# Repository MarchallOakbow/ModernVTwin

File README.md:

# ModernVTwin
The project to make Mesa V-Twin Pedal<br>
First Upload 19th Aug 2016<br>

<li>How to open schematic file</li>
Download CAD soft eagle from here <a href = "https://cadsoft.io/">eagle.io</a><br>
Copy the repository or Download .sch file. And Open it with EagleCAD software.<br>

<li>Current status</li>
The circuit is designed based on the Mesa V-twin.<br>
The power supply & mode switch circuit is changed according to current available parts in Japan.<br>

<li>Changes coming soon...</li>
DRC check<br>
Extract BOM<br>
Parts layout check<br>
Pattern Drawing<br>
PCB design<br>

I would like to foward this project with many hobbyist over the world.<br>
Contact me on twitter <a href = "https://twitter.com/MarChallenge">@MarChallenge</a>.<br>

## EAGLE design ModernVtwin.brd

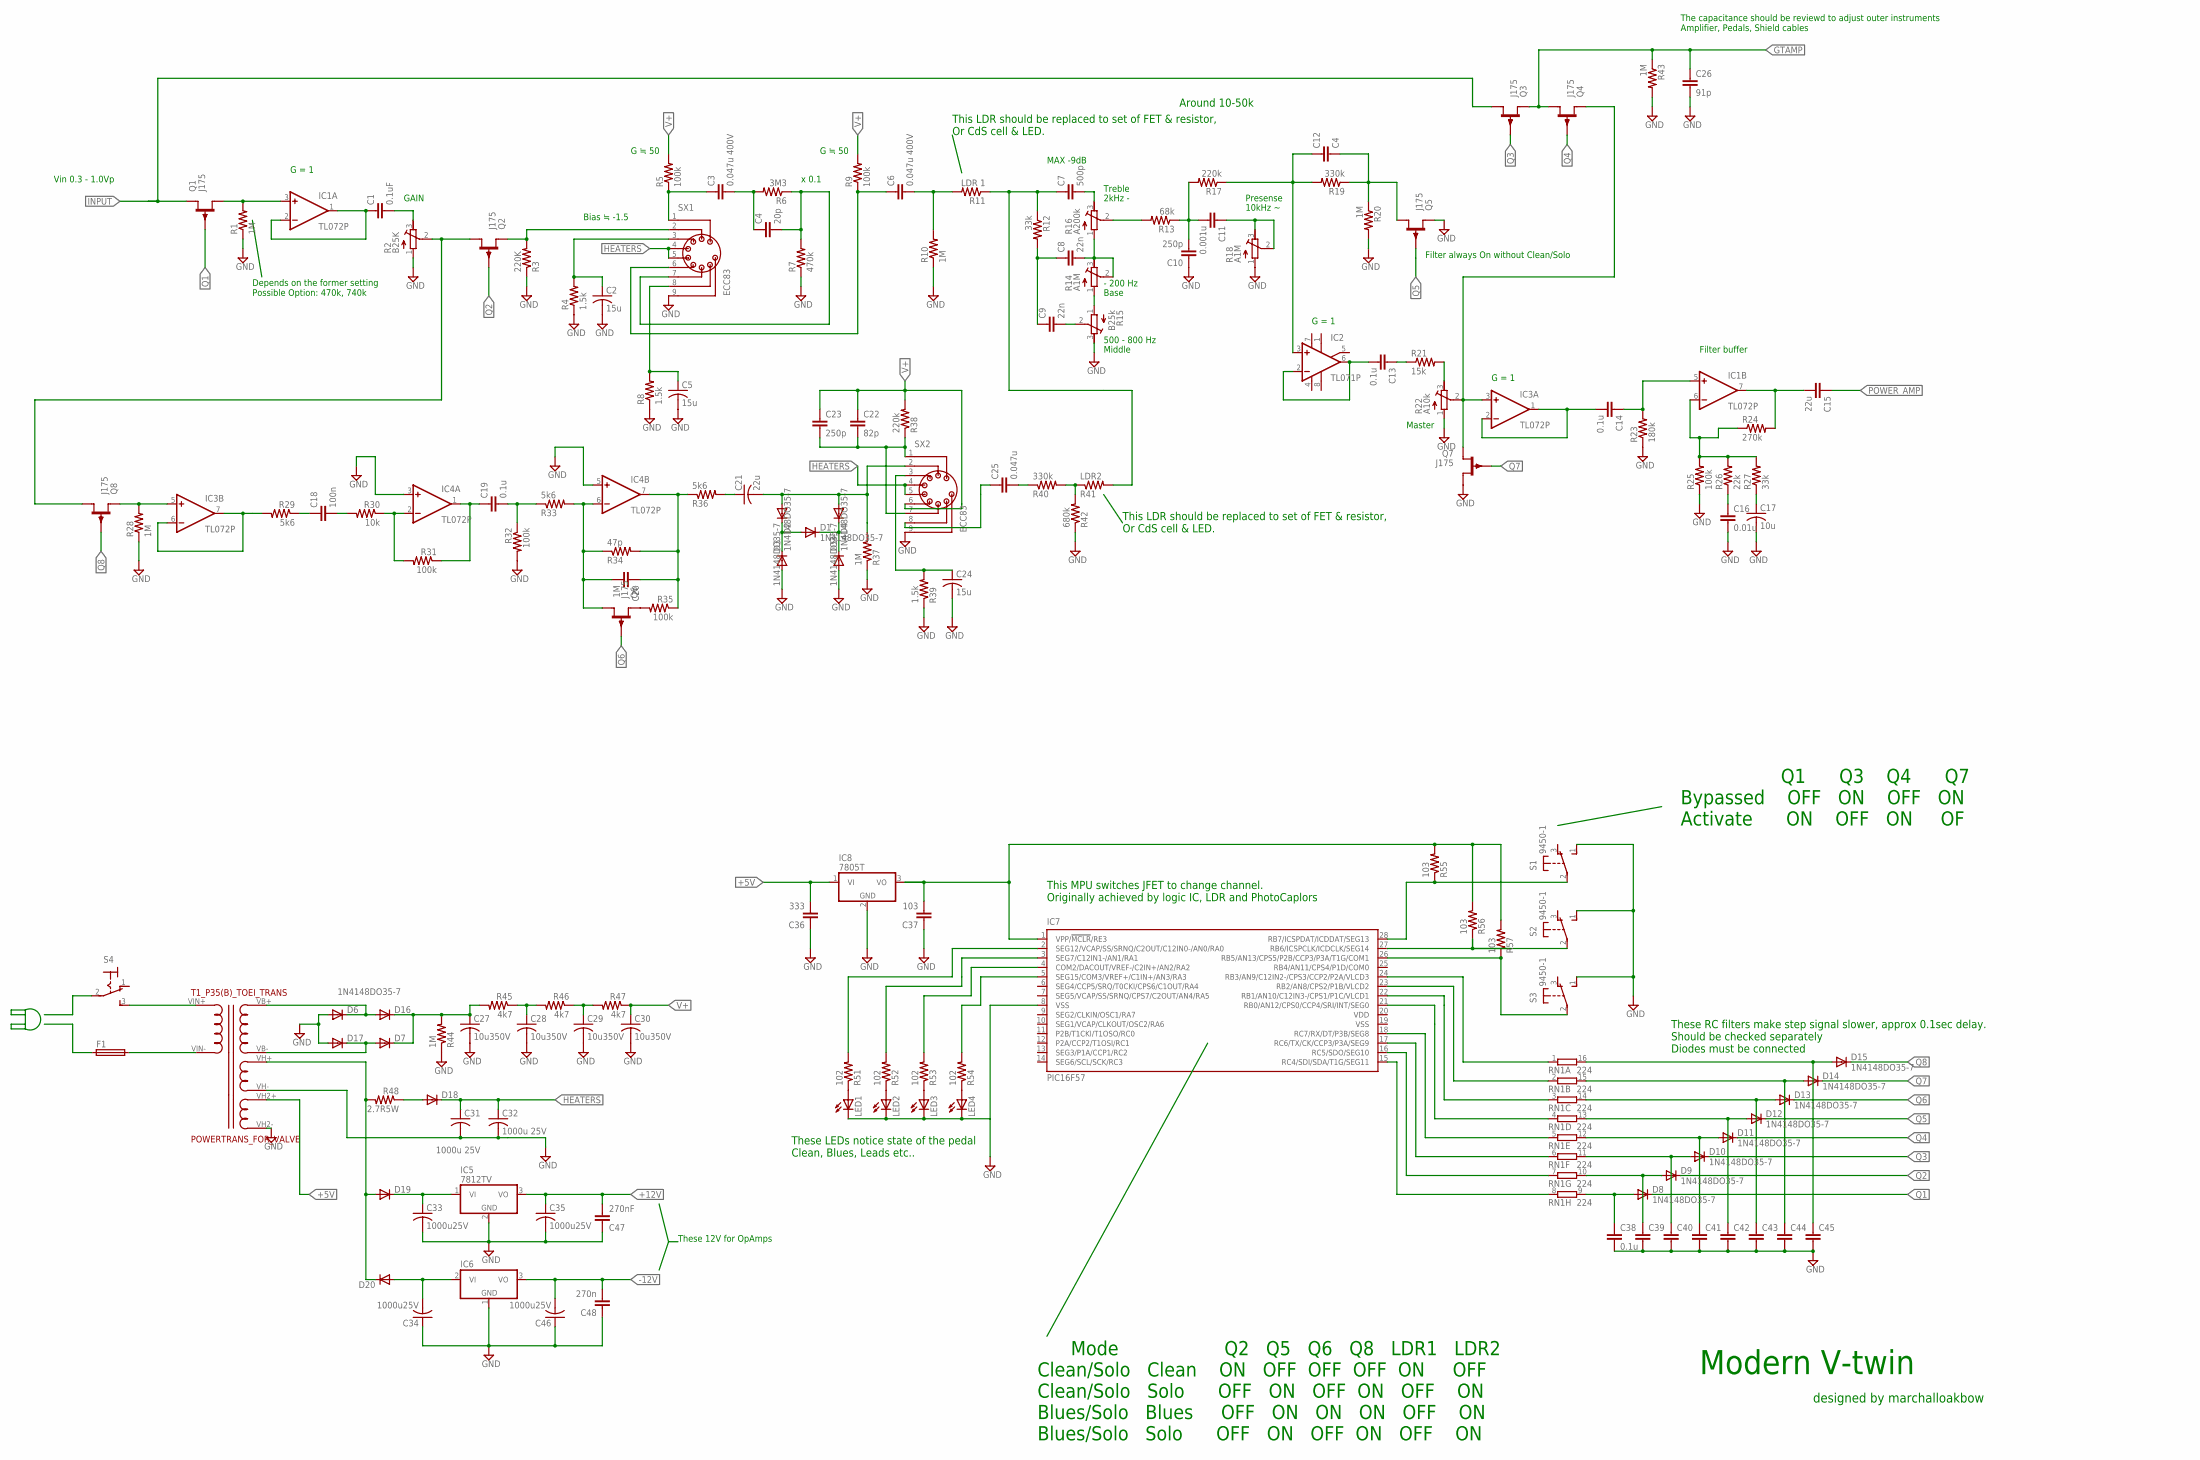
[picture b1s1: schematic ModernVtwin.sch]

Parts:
C1: 0.1uF; C5B3
C2, C5, C24: 15u; C025-025X050
C3, C6: 0.047u 400V; C5B3
C4: 20p; C5B3
C7: 500p; C5B3
C8, C9: 22n; C5B3
C10, C23: 250p; C5B3
C11: 0.001u; C5B3
C12: C4; C5B3
C13, C14, C19: 0.1u; C5B3
C15: 22u; C5B3
C16: 0.01u; C5B3
C17: 10u; C025-025X050
C18: 100n; C5B3
C20: 1M; C5B3
C21: 22u; C025-025X050
C22: 82p; C5B3
C25: 0.047u; C5B3
C26: 91p; C5B3
C27, C28, C29, C30: 10u350V; C025-025X050
C31, C32: 1000u 25V; C025-025X050
C33, C34, C35, C46: 1000u25V; C025-025X050
C36: 333; C5B3
C37: 103; C5B3
C38: 0.1u; C025-024X044
C39, C40, C41, C42, C43, C44, C45: C-EU025-024X044; C025-024X044
C47: 270nF; C5B3
C48: 270n; C5B3
D1, D2, D3, D4, D5, D6, D7, D8, D9, D10, D11, D12, D13, D14, D15, D16, D17, D18, D19, D20: 1N4148DO35-7; DO35-7
F1: SH22,5
IC1, IC3, IC4: TL072P; DIL08
IC2: TL071P; DIL08
IC5: 7812TV; TO220V
IC6: 7912T; TO220H
IC7: PIC16F57; DIL28-3
IC8: 7805T; TO220H
LED1, LED2, LED3, LED4: LED5MM
Q1, Q2, Q3, Q4, Q5, Q6, Q7, Q8: J175; TO92F
R1, R10, R20, R28, R37, R43, R44: 1M; 0204V
R2: B25K; RTRIM64W
R3: 220K; 0204V
R4, R8, R39: 1.5k; 0204V
R5, R9, R25, R31, R32, R35: 100k; 0204V
R6: 3M3; 0204V
R7: 470k; 0204V
R11: LDR 1; 0204V
R12, R27: 33k; 0204V
R13: 68k; 0204V
R14, R18: A1M; RTRIM64W
R15: B25k; RTRIM64W
R16: A200k; RTRIM64W
R17, R38: 220k; 0204V
R19, R40: 330k; 0204V
R21: 15k; 0204V
R22: A10k; RTRIM64W
R23: 180k; 0204V
R24: 270k; 0204V
R26: 22k; 0204V
R29, R33, R36: 5k6; 0204V
R30: 10k; 0204V
R34: 47p; 0204V
R41: LDR2; 0204V
R42: 680k; 0204V
R45, R46, R47: 4k7; 0204V
R48: 2.7R5W; 0204V
R51, R52, R53, R54: 102; 0204V
R55, R56, R57: 103; 0204V
RN1: 224; DIL16
S1, S2, S3: 9450-1
S4: M9040P
SX1, SX2: ECC83; VT9-PT
T1_P35(B)_TOEI_TRANS: POWERTRANS_FOR_VALVE; POWERTRANS

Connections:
+5V: C36.2, IC8.1 (VI), T1_P35(B)_TOEI_TRANS.VH2+
+12V: C35.1, C47.2, IC5.3 (VO)
-12V: C46.2, C48.2, IC6.3 (VO)
GND: C2.2, C5.2, C10.1, C16.2, C17.2, C24.2, C26.2, C27.2, C28.2, C29.2, C30.2, C31.2, C32.2, C33.2, C34.1, C35.2, C36.1, C37.1, C38.2, C39.2, C40.2, C41.2, C42.2, C43.2, C44.2, C45.2, C46.1, C47.1, C48.1, D3.A, D5.A, D6.A, D17.A, IC4.3 (+IN), IC4.5 (+IN), IC5.2 (GND), IC6.1 (GND), IC7.8 (VSS), IC8.2 (GND), LED1.K (C), LED2.K (C), LED3.K (C), LED4.K (C), Q5.S, Q7.D, R1.1, R2.1 (E), R3.1, R4.1, R7.1, R8.1, R10.1, R15.3 (A), R18.1 (E), R20.2, R22.1 (E), R23.1, R25.1, R28.1, R32.2, R37.1, R39.1, R42.1, R43.2, R44.1, S1.1 (S), S2.1 (S), S3.1 (S), SX1.9, SX2.9, T1_P35(B)_TOEI_TRANS.VH2-, T1_P35(B)_TOEI_TRANS.VH-
GTAMP: C26.1, Q3.S, Q4.D, R43.1
HEATERS: C31.1, C32.1, D18.C, SX1.4, SX1.5, SX2.4, SX2.5
INPUT: Q1.S, Q3.D
unnamed: IC1.3 (+IN), Q1.D, R1.2
unnamed: C1.1, IC1.1 (OUT), IC1.2 (-IN)
unnamed: C1.2, R2.3 (A)
unnamed: Q2.D, Q8.D, R2.2 (S)
unnamed: Q2.S, R3.2, SX1.2
unnamed: C2.1, R4.2, SX1.3
unnamed: C3.1, R5.1, SX1.1
unnamed: C3.2, C4.1, R6.2
unnamed: C4.2, R6.1, R7.2, SX1.7
unnamed: R13.2, R16.2 (S)
unnamed: C5.1, R8.2, SX1.8
unnamed: C6.1, R9.1, SX1.6
unnamed: C6.2, R10.2, R11.2
unnamed: C10.2, C11.2, R13.1, R17.2
unnamed: C7.1, R11.1, R12.1, R41.2
unnamed: C8.1, C9.1, R12.2
unnamed: C9.2, R15.2 (S)
unnamed: C8.2, R14.2 (S), R14.3 (A), R16.1 (E)
unnamed: C7.2, R16.3 (A)
unnamed: R14.1 (E), R15.1 (E)
unnamed: C11.1, R18.2 (S), R18.3 (A)
unnamed: C12.1, IC2.3 (+IN), R17.1, R19.2
unnamed: C12.2, Q5.D, R19.1, R20.1
unnamed: IC3.5 (+IN), Q8.S, R28.2
unnamed: C13.2, IC2.2 (-IN), IC2.6 (OUT)
unnamed: C13.1, R21.1
unnamed: R21.2, R22.3 (A)
unnamed: IC3.3 (+IN), Q4.S, Q7.S, R22.2 (S)
unnamed: C14.2, IC3.1 (OUT), IC3.2 (-IN)
unnamed: C14.1, IC1.5 (+IN), R23.2
unnamed: IC1.6 (-IN), R24.1, R25.2, R26.2, R27.2
unnamed: C15.2, IC1.7 (OUT), R24.2
unnamed: C16.1, R26.1
unnamed: C17.1, R27.1
unnamed: IC3.6 (-IN), IC3.7 (OUT), R29.2
unnamed: C18.1, R29.1
unnamed: C18.2, R30.2
unnamed: IC4.2 (-IN), R30.1, R31.2
unnamed: C20.2, IC4.6 (-IN), Q6.D, R33.2, R34.1
unnamed: C19.2, R32.1, R33.1
unnamed: C19.1, IC4.1 (OUT), R31.1
unnamed: Q6.S, R35.2
unnamed: C20.1, IC4.7 (OUT), R34.2, R35.1, R36.1
unnamed: C21.1, R36.2
unnamed: C21.2, D2.A, D4.A, R37.2, SX2.2
unnamed: D1.A, D2.C, D3.C
unnamed: D1.C, D4.C, D5.C
unnamed: C22.2, C23.2, R38.1, SX2.1, SX2.7
unnamed: C25.2, R40.1
unnamed: R40.2, R41.1, R42.2
unnamed: C24.1, R39.2, SX2.3
unnamed: C25.1, SX2.8
unnamed: C37.2, IC7.1 (VPP/!MCLR!/RE3), IC8.3 (VO), R55.2, R56.2, R57.2
unnamed: S4.3 (S), T1_P35(B)_TOEI_TRANS.VIN+ (100VIN+)
unnamed: F1.2, T1_P35(B)_TOEI_TRANS.VIN- (100VIN-)
unnamed: D6.C, D16.A, T1_P35(B)_TOEI_TRANS.VB+
unnamed: D19.A, D20.C, R48.2, T1_P35(B)_TOEI_TRANS.VH+
unnamed: C27.1, D7.C, D16.C, R44.2, R45.2
unnamed: C28.1, R45.1, R46.2
unnamed: IC7.15 (RC4/SDI/SDA/T1G/SEG11), RN1.8 (1)
unnamed: C29.1, R46.1, R47.2
unnamed: D18.A, R48.1
unnamed: IC7.16 (RC5/SDO/SEG10), RN1.7 (1)
unnamed: IC7.17 (RC6/TX/CK/CCP3/P3A/SEG9), RN1.6 (1)
unnamed: IC7.18 (RC7/RX/DT/P3B/SEG8), RN1.5 (1)
unnamed: IC7.21 (RB0/AN12/CPS0/CCP4/SRI/INT/SEG0), RN1.4 (1)
unnamed: IC7.22 (RB1/AN10/C12IN3-/CPS1/P1C/VLCD1), RN1.3 (1)
unnamed: IC7.23 (RB2/AN8/CPS2/P1B/VLCD2), RN1.2 (1)
unnamed: IC7.24 (RB3/AN9/C12IN2-/CPS3/CCP2/P2A/VLCD3), RN1.1
unnamed: IC7.28 (RB7/ICSPDAT/ICDDAT/SEG13), R55.1, S1.2
unnamed: IC7.26 (RB5/AN13/CPS5/P2B/CCP3/P3A/T1G/COM1), R57.1, S3.2
unnamed: LED1.A, R51.1
unnamed: LED2.A, R52.1
unnamed: LED3.A, R53.1
unnamed: LED4.A, R54.1
unnamed: IC7.2 (SEG12/VCAP/SS/SRNQ/C2OUT/C12IN0-/AN0/RA0), R51.2
unnamed: IC7.3 (SEG7/C12IN1-/AN1/RA1), R52.2
unnamed: IC7.4 (COM2/DACOUT/VREF-/C2IN+/AN2/RA2), R53.2
unnamed: IC7.5 (SEG15/COM3/VREF+/C1IN+/AN3/RA3), R54.2
unnamed: C38.1, D8.A, RN1.9 (2)
unnamed: C39.1, D9.A, RN1.10 (2)
unnamed: C40.1, D10.A, RN1.11 (2)
unnamed: C41.1, D11.A, RN1.12 (2)
unnamed: C42.1, D12.A, RN1.13 (2)
unnamed: C43.1, D13.A, RN1.14 (2)
unnamed: C44.1, D14.A, RN1.15 (2)
unnamed: C45.1, D15.A, RN1.16 (2)
unnamed: IC7.27 (RB6/ICSPCLK/ICDCLK/SEG14), R56.1, S2.2
unnamed: D7.A, D17.C, T1_P35(B)_TOEI_TRANS.VB-
unnamed: C33.1, D19.C, IC5.1 (VI)
unnamed: C34.2, D20.A, IC6.2 (VI)
POWER_AMP: C15.1
Q1: D8.C, Q1.G
Q2: D9.C, Q2.G
Q3: D10.C
Q4: D11.C, Q4.G
Q5: D12.C, Q5.G
Q6: D13.C, Q6.G
Q7: D14.C, Q7.G
Q8: D15.C, Q8.G
V+: C22.1, C23.1, C30.1, IC1.8 (V+), IC2.7 (V+), IC3.8 (V+), IC4.8 (V+), R5.2, R9.2, R38.2, R47.1, SX2.6
V-: IC1.4 (V-), IC2.4 (V-), IC3.4 (V-), IC4.4 (V-)
VDD: IC7.20 (VDD)
VSS: IC7.19 (VSS)

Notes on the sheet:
designed by marchalloakbow
Modern V-twin
This LDR should be replaced to set of FET & resistor, Or CdS cell & LED.
Around 10-50k
These LEDs notice state of the pedal Clean, Blues, Leads etc..
This MPU switches JFET to change channel. Originally achieved by logic IC, LDR and PhotoCaplors
These RC filters make step signal slower, approx 0.1sec delay. Should be checked separately Diodes must be connected
Vin 0.3 - 1.0Vp
G = 1
Depends on the former setting Possible Option: 470k, 740k
G ≒ 50
Bias ≒ -1.5
x 0.1
500 - 800 Hz
- 200 Hz
2kHz -
10kHz ~
MAX -9dB
Filter always On without Clean/Solo
GAIN
Treble
Middle
Base
Presense
Master
Filter buffer
The capacitance should be reviewd to adjust outer instruments Amplifier, Pedals, Shield cables
Mode Q2 Q5 Q6 Q8 LDR1 LDR2 Clean/Solo Clean ON OFF OFF OFF ON OFF Clean/Solo Solo OFF ON OFF ON OFF ON Blues/Solo Blues OFF ON ON ON OFF ON Blues/Solo Solo OFF ON OFF ON OFF ON
Q1 Q3 Q4 Q7 Bypassed OFF ON OFF ON Activate ON OFF ON OF
These 12V for OpAmps

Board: 2 copper layers, 152 parts (0 on the bottom side), 107 nets, no tracks yet.

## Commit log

2016-08-20 pics upload
2016-08-20 no message
2016-08-20 edit html
